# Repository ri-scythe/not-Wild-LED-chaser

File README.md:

# Wild-LED-chaser
I want to make this LED chaser for my friend. The silkscreen drawing was drawn by me :D

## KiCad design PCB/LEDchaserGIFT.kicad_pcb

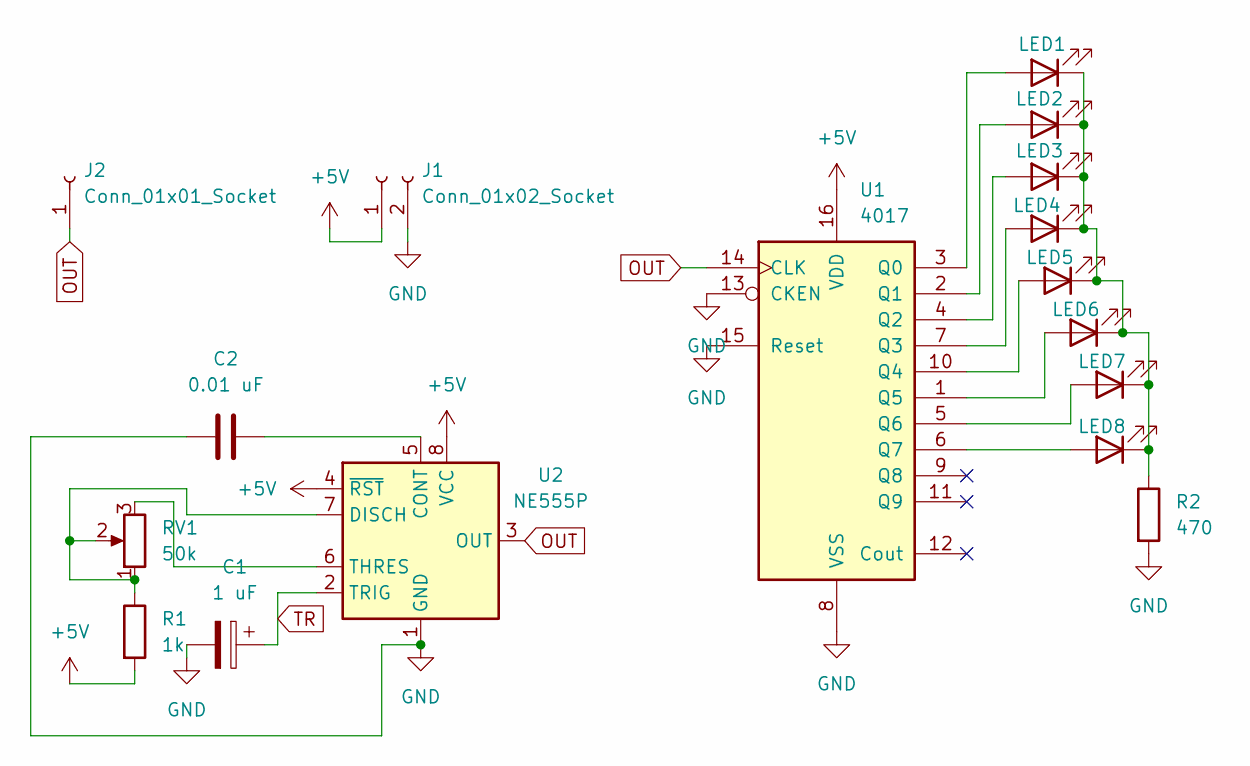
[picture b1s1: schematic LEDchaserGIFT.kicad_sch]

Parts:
C1: 1 uF; CP_Radial_D5.0mm_P2.00mm
C2: 0.01 uF; C_Disc_D7.5mm_W2.5mm_P5.00mm
D1: LED1; LED_D3.0mm
D2: LED2; LED_D3.0mm
D3: LED3; LED_D3.0mm
D4: LED4; LED_D3.0mm
D5: LED5; LED_D3.0mm
D6: LED6; LED_D3.0mm
D7: LED7; LED_D3.0mm
D8: LED8; LED_D3.0mm
J1: Conn_01x02_Socket; PinHeader_1x02_P2.54mm_Vertical
J2: Conn_01x01_Socket; PinHeader_1x01_P2.54mm_Vertical
R1: 1k; R_Axial_DIN0207_L6.3mm_D2.5mm_P7.62mm_Horizontal
R2: 470; R_Axial_DIN0207_L6.3mm_D2.5mm_P7.62mm_Horizontal
RV1: 50k; Potentiometer_Vishay_T93YA_Vertical
U1: 4017; N16
U2: NE555P; DIP-8_W7.62mm

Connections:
+5V: J1.1, R1.2, U1.16 (VDD), U2.4 (~RST), U2.8 (VCC)
GND: C1.2, C2.1, J1.2, R2.2, U1.8 (VSS), U1.13 (CKEN), U1.15 (Reset), U2.1 (GND)
unnamed: D1.2 (A), U1.3 (Q0)
unnamed: D1.1 (K), D2.1 (K), D3.1 (K), D4.1 (K), D5.1 (K), D6.1 (K), D7.1 (K), D8.1 (K), R2.1
unnamed: D2.2 (A), U1.2 (Q1)
unnamed: D3.2 (A), U1.4 (Q2)
unnamed: D4.2 (A), U1.7 (Q3)
unnamed: D5.2 (A), U1.10 (Q4)
unnamed: D6.2 (A), U1.1 (Q5)
unnamed: D7.2 (A), U1.5 (Q6)
unnamed: D8.2 (A), U1.6 (Q7)
unnamed: C2.2, U2.5 (CONT)
unnamed: R1.1, RV1.1, RV1.2, U2.7 (DISCH)
unnamed: RV1.3, U2.6 (THRES)
OUT: J2.1, U1.14 (CLK), U2.3 (OUT)
TR: C1.1, U2.2 (TRIG)

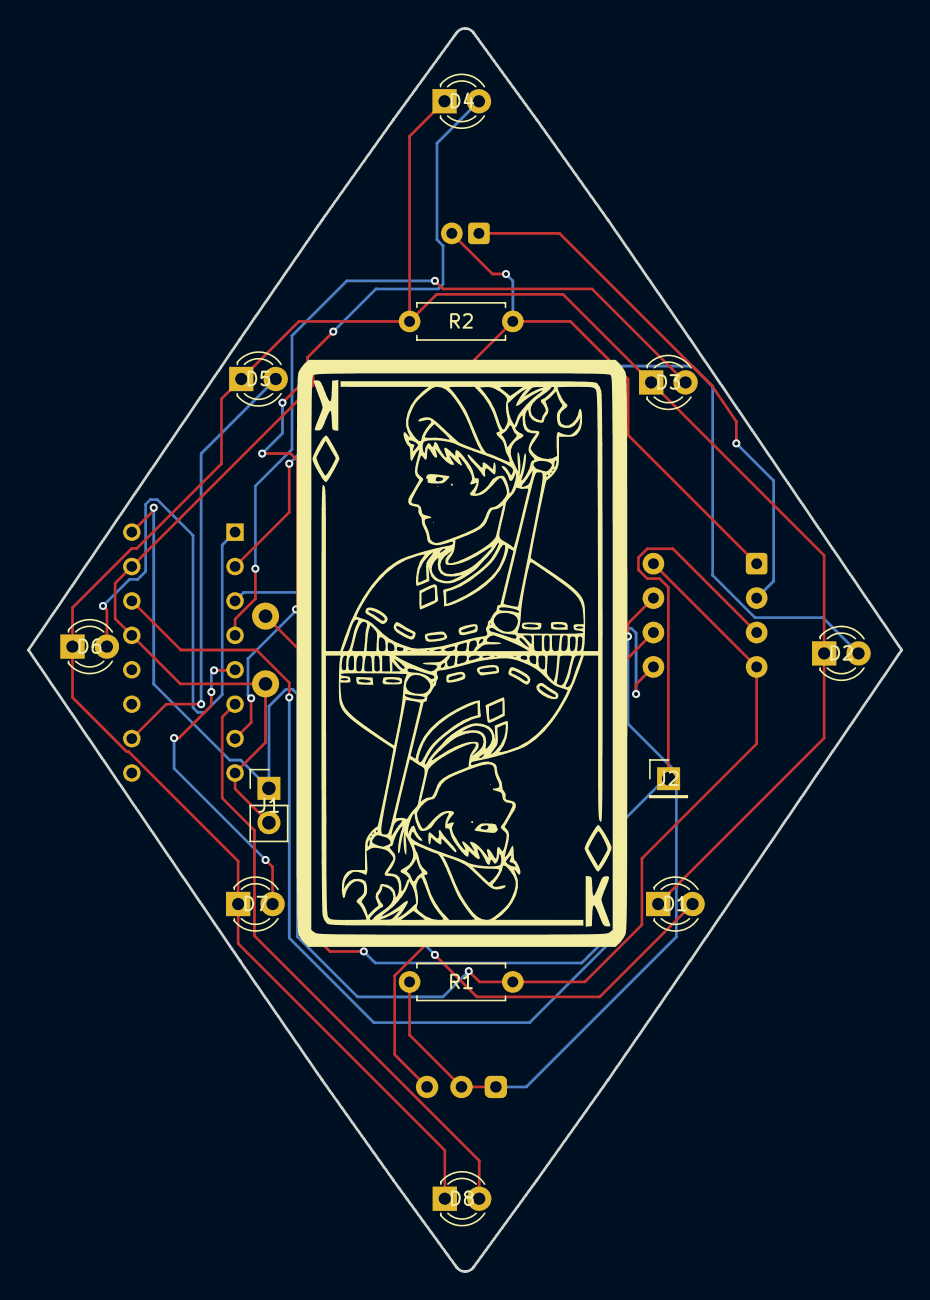
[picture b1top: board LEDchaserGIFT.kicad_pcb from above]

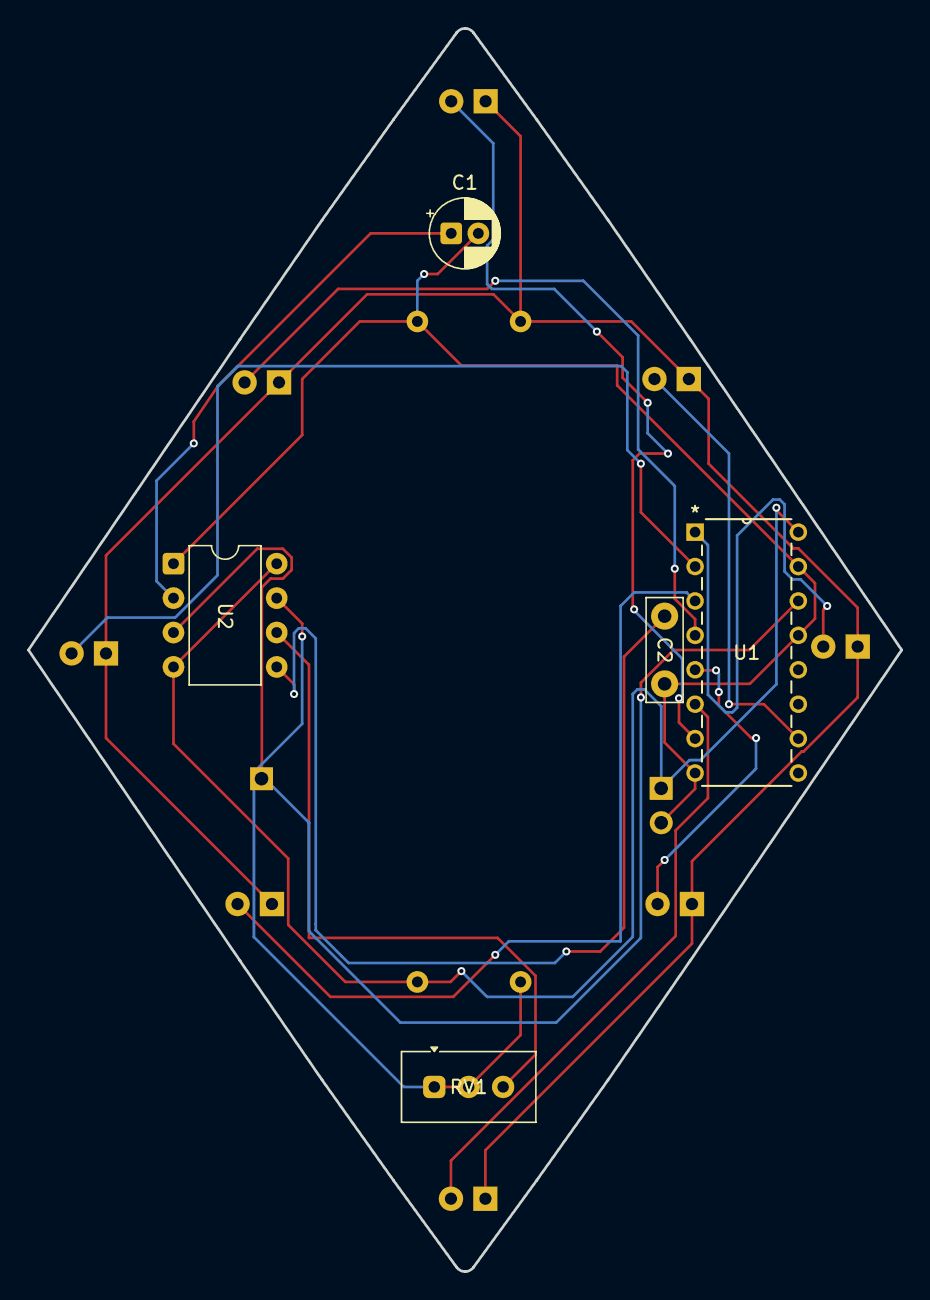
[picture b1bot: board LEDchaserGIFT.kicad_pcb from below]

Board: 2 copper layers, 64.5 x 91.8 mm, 17 parts (5 on the bottom side), 16 nets.

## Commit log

2026-03-23 Create A
2026-03-23 Create ss
2026-03-23 Fix link formatting for BOM section in README
2026-03-23 Create s
2026-03-24 Add image references to README.md
